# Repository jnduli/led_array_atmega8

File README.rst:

LED ARRAY CIRCUIT
=================

Story
-----
Doe wants to create a lights system where text moves from right to
left. He wants to it to be as easy as possible. Also, should he
decide the text to change it should be possible to change.

At some point too, he decides he wants an animation of lights. The
system should also have capabilities to enable that.

Specification
-------------

1. LEDs that can scroll on the side
2. Easy to change the LEDs text
3. Easy to change the text being shown

For fat support in microsd cards check:
http://elm-chan.org/fsw/ff/00index_e.html

Links used in the design
------------------------

TODO
----

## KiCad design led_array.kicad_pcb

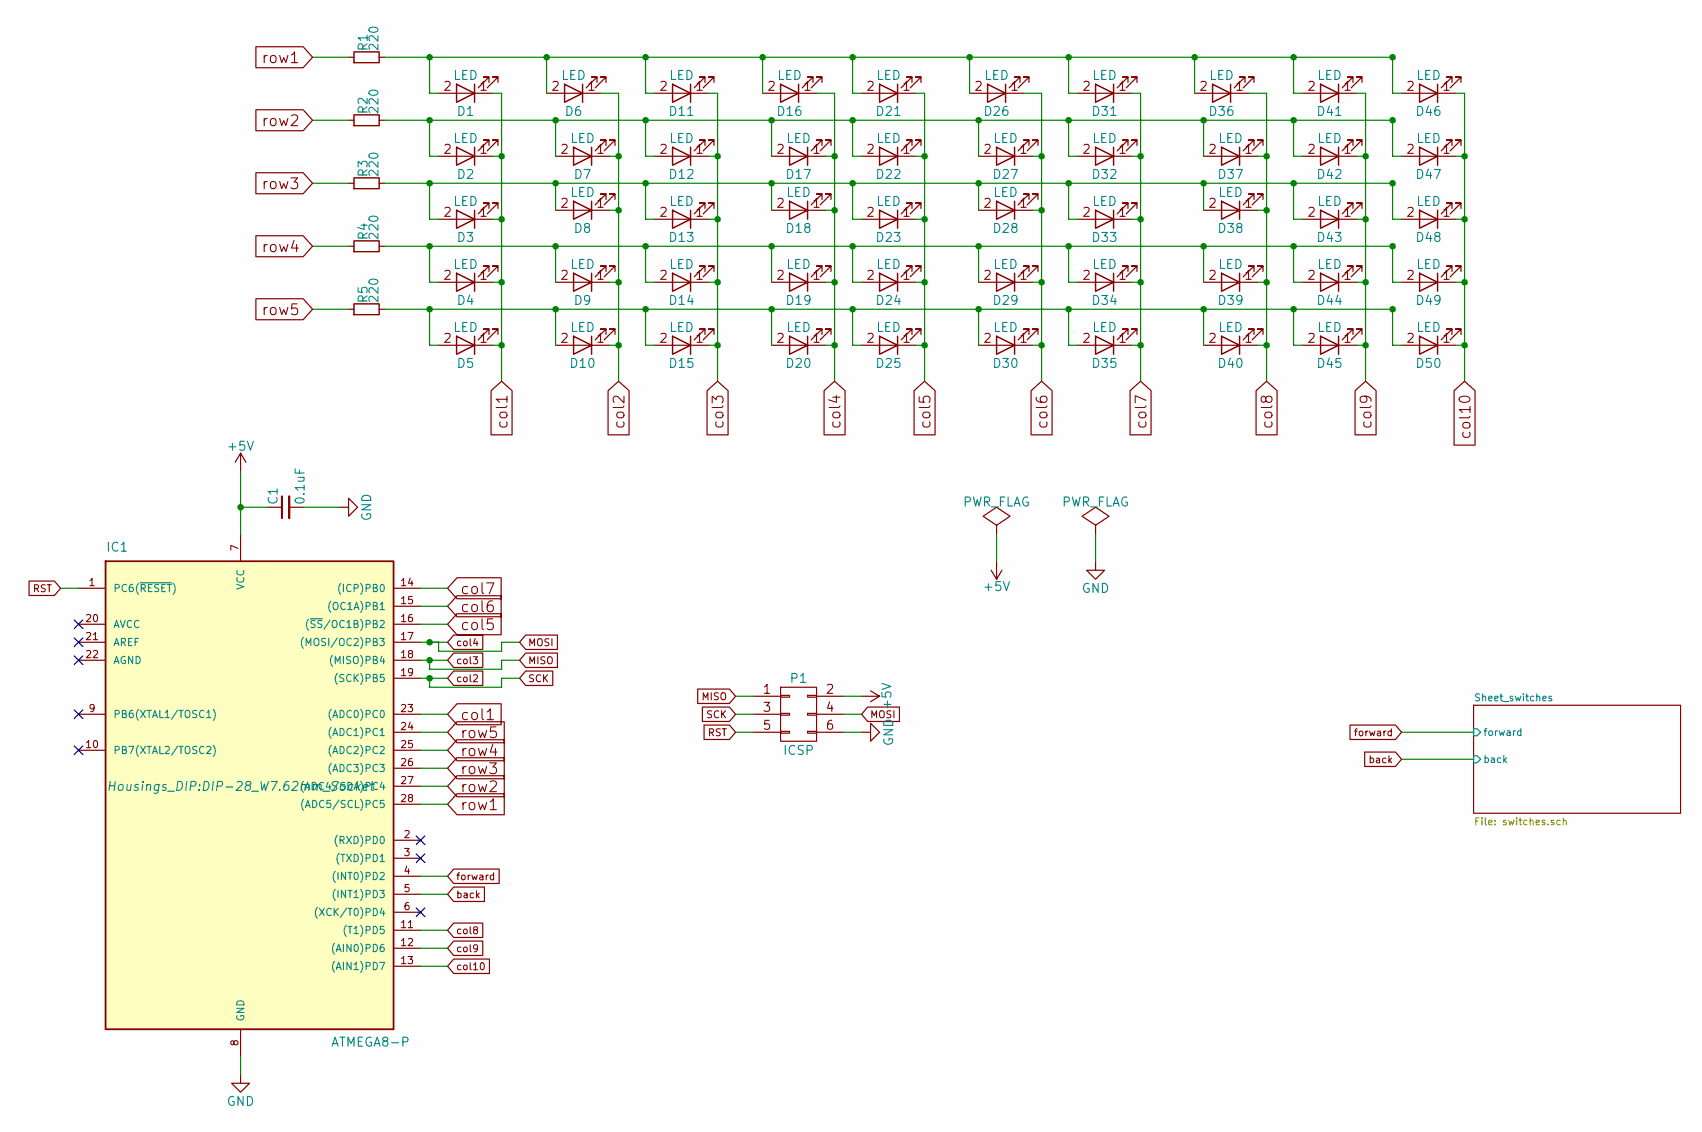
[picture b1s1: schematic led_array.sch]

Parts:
C1: 0.1uF; C_Disc_D3.0mm_W1.6mm_P2.50mm
D1, D2, D3, D4, D5, D6, D7, D8, D9, D10, D11, D12, D13, D14, D15, D16, D17, D18, D19, D20, D21, D22, D23, D24, D25, D26, D27, D28, D29, D30, D31, D32, D33, D34, D35, D36, D37, D38, D39, D40, D41, D42, D43, D44, D45, D46, D47, D48, D49, D50: LED; LED_D3.0mm
IC1: ATMEGA8-P; DIP-28_W7.62mm_Socket
P1: ICSP; IDC_Header_Straight_6pins
R1, R2, R3, R4, R5: 220; R1

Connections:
+5V: C1.1, IC1.7 (VCC), P1.2; also elsewhere on the board
GND: C1.2, IC1.8 (GND), P1.6; also elsewhere on the board
MISO: D11.1 (K), D12.1 (K), D13.1 (K), D14.1 (K), D15.1 (K), IC1.18 ((MISO)PB4), P1.1
MOSI: D16.1 (K), D17.1 (K), D18.1 (K), D19.1 (K), D20.1 (K), IC1.17 ((MOSI/OC2)PB3), P1.4
unnamed: D1.2 (A), D6.2 (A), D11.2 (A), D16.2 (A), D21.2 (A), D26.2 (A), D31.2 (A), D36.2 (A), D41.2 (A), D46.2 (A), R1.2
unnamed: D5.2 (A), D10.2 (A), D15.2 (A), D20.2 (A), D25.2 (A), D30.2 (A), D35.2 (A), D40.2 (A), D45.2 (A), D50.2 (A), R5.2
unnamed: D2.2 (A), D7.2 (A), D12.2 (A), D17.2 (A), D22.2 (A), D27.2 (A), D32.2 (A), D37.2 (A), D42.2 (A), D47.2 (A), R2.2
unnamed: D3.2 (A), D8.2 (A), D13.2 (A), D18.2 (A), D23.2 (A), D28.2 (A), D33.2 (A), D38.2 (A), D43.2 (A), D48.2 (A), R3.2
unnamed: D4.2 (A), D9.2 (A), D14.2 (A), D19.2 (A), D24.2 (A), D29.2 (A), D34.2 (A), D39.2 (A), D44.2 (A), D49.2 (A), R4.2
RST: IC1.1 (PC6(~RESET~)), P1.5
SCK: D6.1 (K), D7.1 (K), D8.1 (K), D9.1 (K), D10.1 (K), IC1.19 ((SCK)PB5), P1.3
back: IC1.5 ((INT1)PD3); also elsewhere on the board
col1: D1.1 (K), D2.1 (K), D3.1 (K), D4.1 (K), D5.1 (K), IC1.23 ((ADC0)PC0)
col5: D21.1 (K), D22.1 (K), D23.1 (K), D24.1 (K), D25.1 (K), IC1.16 ((~SS~/OC1B)PB2)
col6: D26.1 (K), D27.1 (K), D28.1 (K), D29.1 (K), D30.1 (K), IC1.15 ((OC1A)PB1)
col7: D31.1 (K), D32.1 (K), D33.1 (K), D34.1 (K), D35.1 (K), IC1.14 ((ICP)PB0)
col8: D36.1 (K), D37.1 (K), D38.1 (K), D39.1 (K), D40.1 (K), IC1.11 ((T1)PD5)
col9: D41.1 (K), D42.1 (K), D43.1 (K), D44.1 (K), D45.1 (K), IC1.12 ((AIN0)PD6)
col10: D46.1 (K), D47.1 (K), D48.1 (K), D49.1 (K), D50.1 (K), IC1.13 ((AIN1)PD7)
forward: IC1.4 ((INT0)PD2); also elsewhere on the board
row1: IC1.28 ((ADC5/SCL)PC5), R1.1
row2: IC1.27 ((ADC4/SDA)PC4), R2.1
row3: IC1.26 ((ADC3)PC3), R3.1
row4: IC1.25 ((ADC2)PC2), R4.1
row5: IC1.24 ((ADC1)PC1), R5.1

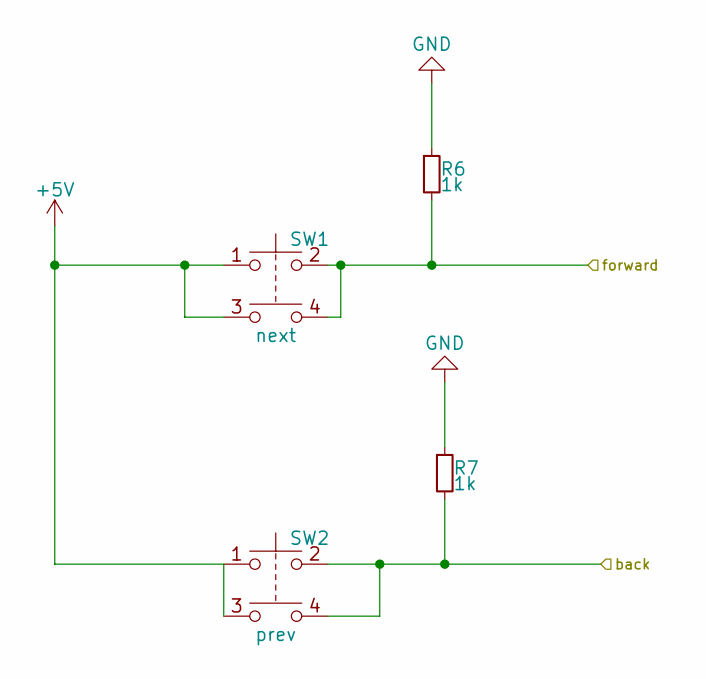
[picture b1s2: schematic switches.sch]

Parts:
R6, R7: 1k; R1
SW1: next; SW_TH_Tactile_Omron_B3F-10xx
SW2: prev; SW_TH_Tactile_Omron_B3F-10xx

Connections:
+5V: SW1.1, SW1.3, SW2.1, SW2.3; also elsewhere on the board
GND: R6.1, R7.1; also elsewhere on the board
back: R7.2, SW2.2, SW2.4; also elsewhere on the board
forward: R6.2, SW1.2, SW1.4; also elsewhere on the board

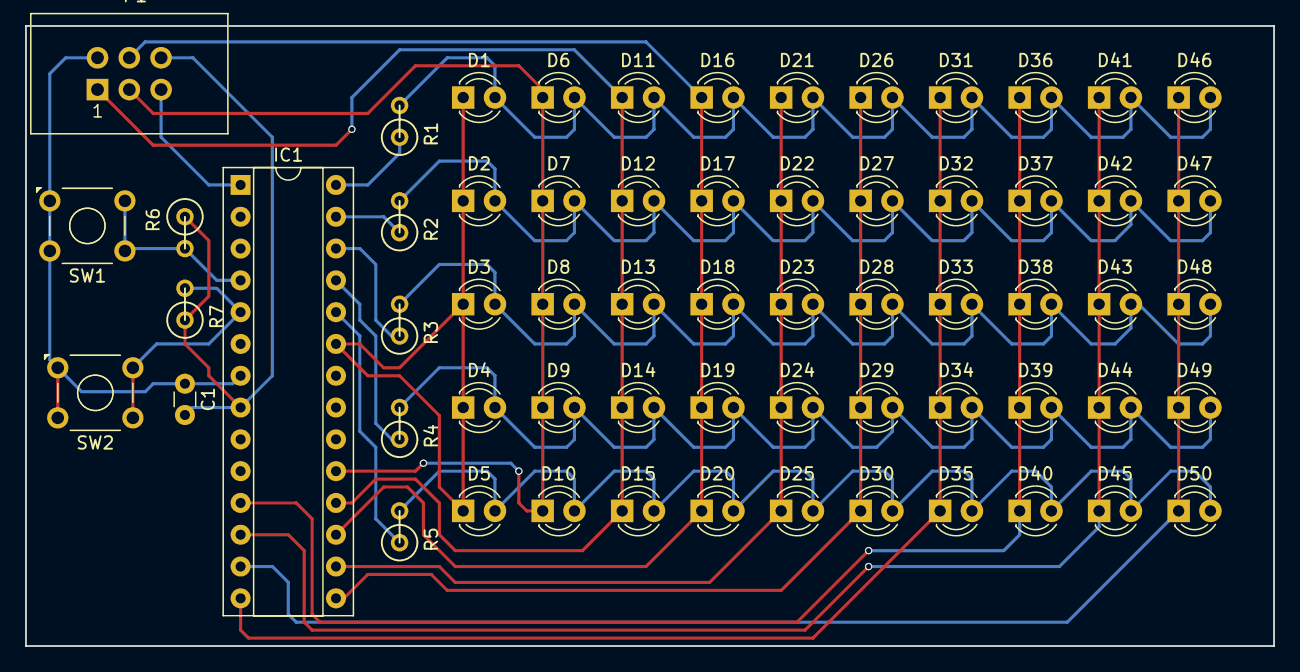
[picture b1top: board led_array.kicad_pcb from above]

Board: 2 copper layers, 99.7 x 49.5 mm, 62 parts (0 on the bottom side), 25 nets.

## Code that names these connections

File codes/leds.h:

#define row1 PC5
#define row2 PC4
#define row3 PC3
#define row4 PC2
#define row5 PC1

#define col1 PC0
#define col2 PB5
#define col3 PB4
#define col4 PB3
#define col5 PB2
#define col6 PB1
#define col7 PB0
#define col8 PD5
#define col9 PD6
#define col10 PD7

#include <avr/io.h>

const int rows_pins[] = {PC5, PC4, PC3, PC2, PC1};
const int cols_pins[] = {PC0, PB5, PB4, PB3, PB2, PB1, PB0, PD5, PD6, PD7};


#define rows 5
#define cols 10
class Leds
{
    public:
        Leds ();
        void lightLED ( int row, int col );
        void turnOffLED ( int row, int col );
        void lightAllLEDs ();
        void turnOffAllLEDs();
        void drawCharacter ( const int A [3][5]);
        void drawBuffer();
        void makePattern( int j);
        void drawPattern();
        void setColumn(int a, int b);

        //variables
        //
        static const int buffer_row = 5;
        static const int buffer_col = 10;
        static const int pattern_col = 48;
        volatile int8_t buffer [buffer_row][buffer_col] = {
            {1,0,1,0,1,0,1,1,0,1},
            {1,0,1,1,0,1,1,0,1,1},
            {1,1,1,1,1,1,1,1,0,1},
            {1,0,1,1,0,1,1,0,0,1},
            {1,0,1,1,0,1,1,0,0,1}
        };
        //int pattern [buffer_row][buffer_col] = {
            //{1,0,1,0,1,0,1,1,0,1},
            //{1,0,1,1,0,1,1,0,1,1},
            //{1,1,1,1,1,1,1,1,0,1},
            //{1,0,1,1,0,1,1,0,0,1},
            //{1,0,1,1,0,1,1,0,0,1}
        //};
        const uint8_t pattern [buffer_row][pattern_col] ={
            {1,0,1,0,0,1,0,0,1,1,0,0,1,1,0,0,1,0,1,0,0,0,1,1,1,0,0,1,0,0,0,1,1,0,1,1,1,0,1,1,1,0,1,1,0,0,0,0},
            {1,0,1,0,1,0,1,0,1,0,1,0,1,0,1,0,1,0,1,0,0,0,1,0,0,0,1,0,1,0,1,0,0,0,0,1,0,0,1,0,0,0,1,0,1,0,0,0},
            {1,1,1,0,1,1,1,0,1,1,0,0,1,1,0,0,1,1,1,0,0,0,1,1,1,0,1,1,1,0,0,1,0,0,0,1,0,0,1,1,1,0,1,1,0,0,0,0},
            {1,0,1,0,1,0,1,0,1,0,0,0,1,0,0,0,0,0,1,0,0,0,1,0,0,0,1,0,1,0,0,0,1,0,0,1,0,0,1,0,0,0,1,0,1,0,0,0},
            {1,0,1,0,1,0,1,0,1,0,0,0,1,0,0,0,1,1,0,0,0,0,1,1,1,0,1,0,1,0,1,1,0,0,0,1,0,0,1,1,1,0,1,0,1,0,0,0}
        };
        const int H [3][5] = {
            {1,1,1,1,1},
            {0,0,1,0,0},
            {1,1,1,1,1}
        };
        const int A [3][5] = {
            {0,1,1,1,1},
            {1,0,1,0,0},
            {0,1,1,1,1}
        };
        const int P [3][5] = {
            {1,1,1,1,1},
            {1,0,1,0,0},
            {0,1,0,0,0}
        };
        const int Y [3][5] = {
            {1,1,1,0,1},
            {0,0,1,0,1},
            {1,1,1,1,0}
        };
        const int E [3][5] = {
            {1,1,1,1,1},
            {1,0,1,0,1},
            {1,0,1,0,1}
        };
        const int S [3][5] = {
            {0,1,0,0,1},
            {1,0,1,0,1},
            {1,0,0,1,0}
        };
        const int T [3][5] = {
            {1,0,0,0,0},
            {1,1,1,1,1},
            {1,0,0,0,0}
        };
        const int R [3][5] = {
            {1,1,1,1,1},
            {1,0,1,0,0},
            {0,1,0,1,1}
        };
};

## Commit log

2017-02-19 Array of LEDs project started
2017-02-19 Added a microcontroller atmega 8 to the project. Also added a 2X# connector to program the project
2017-03-01 Various changes made to LED pcb
2017-03-21 COmpleted routing of LEDs. Other stuff were done before this but I forgot to commit
2017-03-23 Small changes made to the schematic
2017-03-23 Added gerber files sent to elecrow for pcb making
2017-04-16 Make file. Changes made to program using usbasp
2017-04-16 LED arrays. Currently shows some letters
2017-04-16 Added extras of gcc to gitignore and also .swp
2017-04-16 Fixed all the errors from compiling. Now its displaying characters well
2017-04-16 Refactored code to make code that displays characters a function
2017-04-16 Changed the programmer to usbasp from usbasp-clone and compiler to gcc
2017-04-16 Make turnoffLEd work well, make animation smoother, changed pattern to show happy easter
